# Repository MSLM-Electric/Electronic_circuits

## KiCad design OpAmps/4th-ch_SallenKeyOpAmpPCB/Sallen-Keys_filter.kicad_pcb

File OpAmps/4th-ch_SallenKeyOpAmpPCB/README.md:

!!! PROJECT'S STATUS !!!
Projects is not completed yet.
In progress!
Not tested!

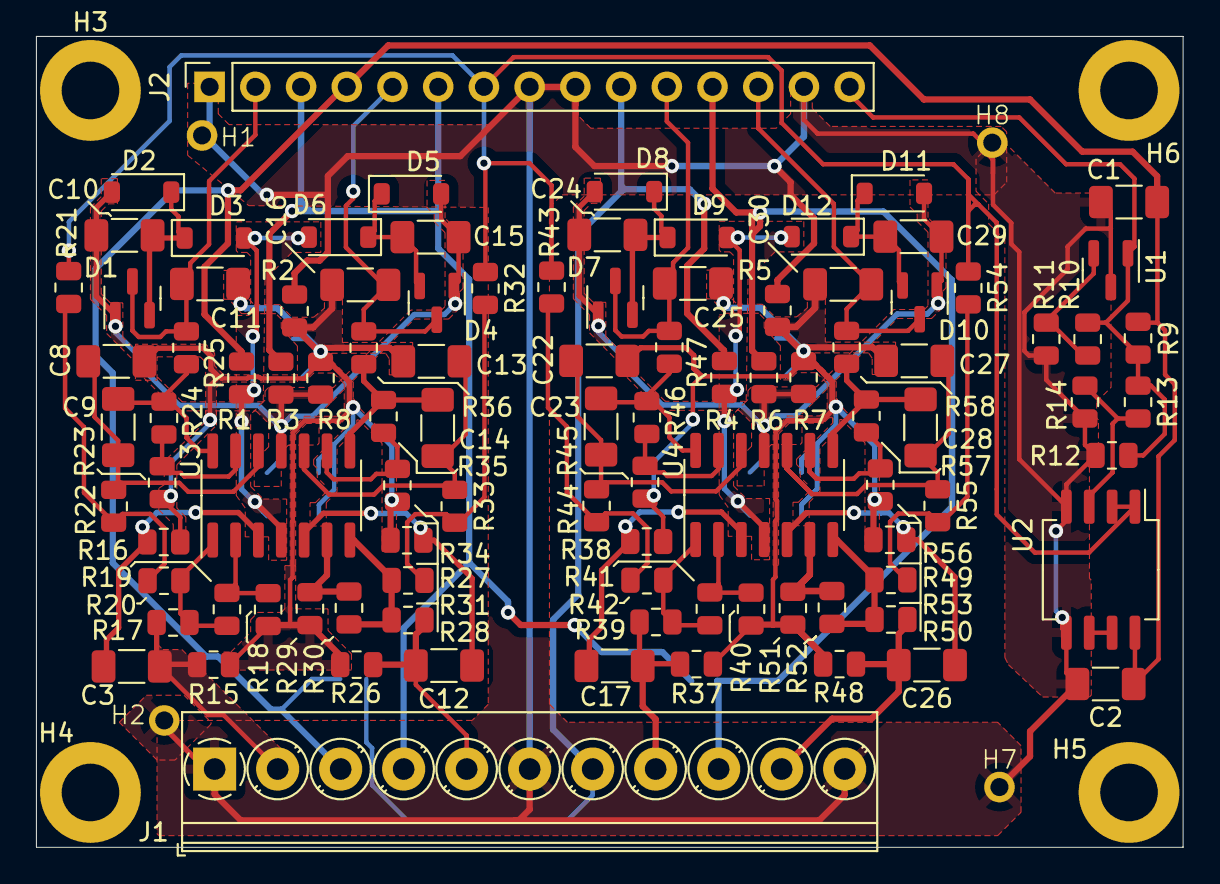
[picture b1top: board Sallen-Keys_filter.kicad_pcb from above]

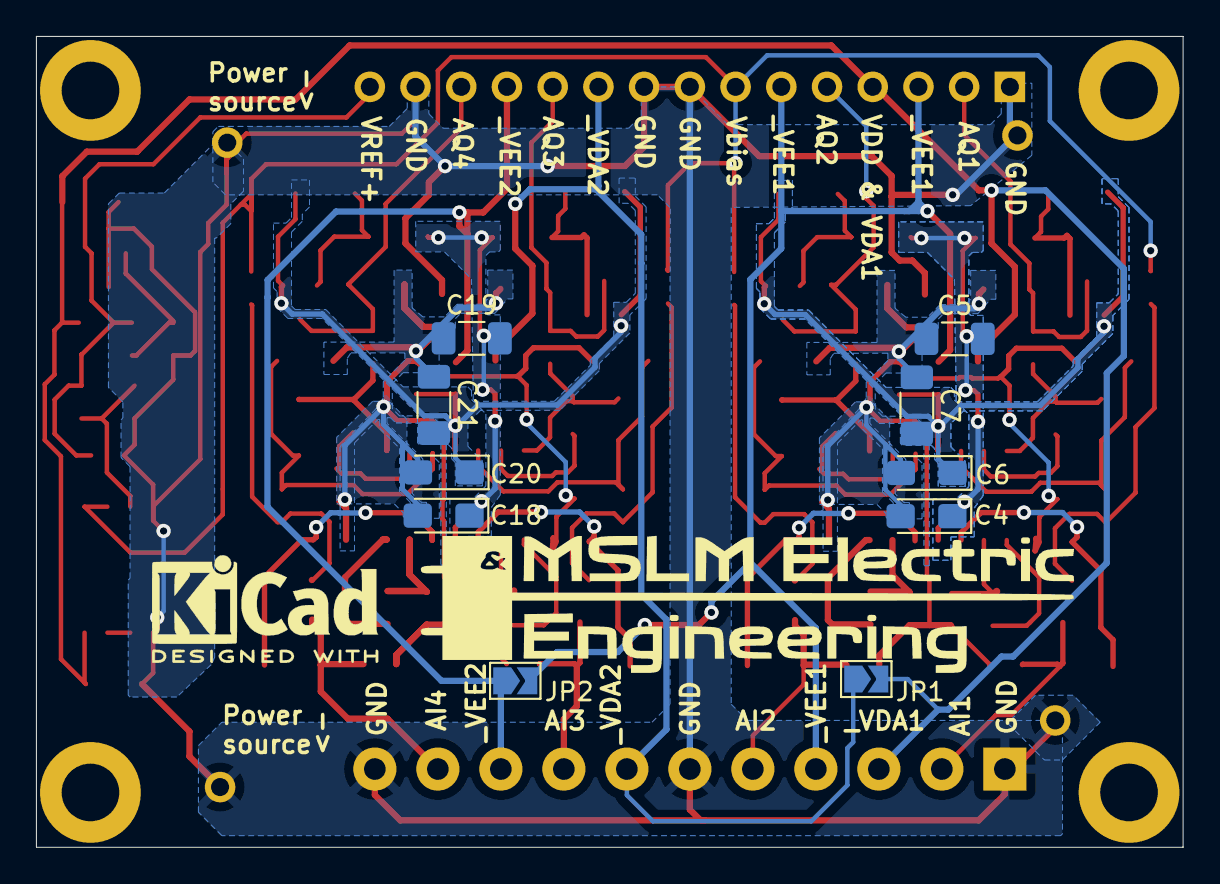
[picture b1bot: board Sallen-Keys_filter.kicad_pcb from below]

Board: 2 copper layers, 63.7 x 45.0 mm, 116 parts (10 on the bottom side), 56 nets.

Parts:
C1, C2, C3, C5, C7, C8, C9, C10, C11, C12, C13, C14, C15, C16, C17, C19, C21, C22, C23, C24, C25, C26, C27, C28, C29, C30: C_Small; C_1206_3216Metric_Pad1.33x1.80mm_HandSolder
C4, C6, C18, C20: CP_Small; CP_EIA-3216-10_Kemet-I_Pad1.58x1.35mm_HandSolder
D1, D4, D7, D10: BAT54S; SOT-23
D2, D5, D8, D11: BZT52C15 /5V1..6/C10; D_SOD-123
D3, D6, D9, D12: 1N4148; D_SOD-123
H1, H2, H7, H8: MountingHole_Pad_small; Hole_pad_1mm
H3, H4, H5, H6: MountingHole_Pad; MountingHole_3.2mm_M3_DIN965_Pad
J1: Screw_Terminal_01x11; TerminalBlock_Phoenix_PT-1,5-11-3.5-H_1x11_P3.50mm_Horizont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
J2: Conn_01x15; PinSocket_1x15_P2.54mm_Vertical
JP1, JP2: Jumper_NC_Small; SolderJumper-2_P1.3mm_Open_TrianglePad1.0x1.5mm
R1, R2, R3, R4, R5, R6: 0R; R_0805_2012Metric
R7, R8: NP; R_0805_2012Metric
R9, R10, R11, R12, R13, R14, R15, R16, R17, R18, R19, R20, R21, R22, R23, R24, R25, R26, R27, R28, R29, R30, R31, R32, R33, R34, R35, R36, R37, R38, R39, R40, R41, R42, R43, R44, R45, R46, R47, R48, R49, R50, R51, R52, R53, R54, R55, R56, R57, R58: R_Small; R_0805_2012Metric
U1: TL431DBZ; SOT-23
U2: LM358; SO-8_5.3x6.2mm_P1.27mm
U3, U4: Opamp_Quad_Generic; SOIC-14_3.9x8.7mm_P1.27mm

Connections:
/AI1: C3.2, J1.2, R15.2, R17.1
/AI2: C12.2, J1.5, R26.2, R28.1
/AI3: C17.2, J1.8, R37.2, R39.1
/AI4: C26.2, J1.10, R48.2, R50.1
/AQ1: C11.2, D1.3 (common), J2.2, R25.1
/AQ2: C16.2, D4.3 (common), J2.5, R36.1
/AQ3: C25.2, D7.3 (common), J2.11, R47.1
/AQ4: C30.2, D10.3 (common), J2.13, R58.1
/OPA1GND: C4.2, C5.1, C6.2, C7.1, C8.1, C11.1, C13.1, C16.1, R2.2, R8.1, R15.1, R16.1, R18.1, R23.1, R26.1, R27.1, R29.1, R34.1
/OPA1VDA: C4.1, C5.2, D3.2 (A), D6.2 (A), R1.2, U3.4 (V+)
/OPA1VEE: C6.1, C7.2, C10.1, C15.1, D1.1 (A), D2.2 (A), D4.1 (A), D5.2 (A), R3.2, R8.2, U3.11 (V-)
/OPA2GND: C18.2, C19.1, C20.2, C21.1, C22.1, C25.1, C27.1, C30.1, R5.2, R7.1, R37.1, R38.1, R40.1, R45.1, R48.1, R49.1, R51.1, R56.1
/OPA2VDA: C18.1, C19.2, D9.2 (A), D12.2 (A), R4.2, U4.4 (V+)
/OPA2VEE: C20.1, C21.2, C24.1, C29.1, D7.1 (A), D8.2 (A), D10.1 (A), D11.2 (A), R6.2, R7.2, U4.11 (V-)
/VBIAS1/EN: C1.1, C2.1, J1.3, J2.4, JP1.2, R1.1, R9.2, U2.8 (V+)
/VREF+: J2.15, R9.1, R10.1, R12.1, R13.1, U1.1 (K)
/bias: J2.7, R21.1, R32.1, R43.1, R54.1, U2.1, U2.2 (-)
GNDD: C1.2, C2.2, H1.1, H2.1, H7.1, H8.1, J1.1, J1.6, J1.11, J2.1, J2.8, J2.9, J2.14, R2.1, R5.1, R11.2, R12.2, R14.2, U1.3 (A), U2.4 (V-), U2.5 (+)
unnamed: C9.1, R24.1, R25.2, U3.14
unnamed: C14.1, R35.1, R36.2, U3.8
unnamed: C23.1, R46.1, R47.2, U4.14
unnamed: C28.1, R57.1, R58.2, U4.8
unnamed: C10.2, D1.2 (K), D2.1 (K), D3.1 (K)
unnamed: C15.2, D4.2 (K), D5.1 (K), D6.1 (K)
unnamed: C24.2, D7.2 (K), D8.1 (K), D9.1 (K)
unnamed: C29.2, D10.2 (K), D11.1 (K), D12.1 (K)
unnamed: J1.4, J2.3, J2.6, JP2.2, R3.1
unnamed: J1.7, J2.10, JP1.1, R4.1
unnamed: J1.9, J2.12, JP2.1, R6.1
unnamed: R17.2, R19.1, R20.2, U3.1
unnamed: R20.1, R21.2, R22.2
unnamed: R28.2, R30.1, R31.2, U3.7
unnamed: R31.1, R32.2, R33.2
unnamed: R39.2, R41.1, R42.2, U4.1
unnamed: R42.1, R43.2, R44.2
unnamed: R50.2, R52.1, R53.2, U4.7
unnamed: R53.1, R54.2, R55.2
unnamed: R10.2, R11.1, U1.2 (REF)
unnamed: R13.2, R14.1, U2.3 (+)
unnamed: U2.6 (-), U2.7
unnamed: C3.1, R16.2, U3.3 (+)
unnamed: R18.2, R19.2, U3.2 (-)
unnamed: C12.1, R27.2, U3.5 (+)
unnamed: R29.2, R30.2, U3.6 (-)
unnamed: C13.2, C14.2, R33.1, U3.10 (+)
unnamed: R34.2, R35.2, U3.9 (-)
unnamed: C8.2, C9.2, R22.1, U3.12 (+)
unnamed: R23.2, R24.2, U3.13 (-)
unnamed: C17.1, R38.2, U4.3 (+)
unnamed: R40.2, R41.2, U4.2 (-)
unnamed: C26.1, R49.2, U4.5 (+)
unnamed: R51.2, R52.2, U4.6 (-)
unnamed: C27.2, C28.2, R55.1, U4.10 (+)
unnamed: R56.2, R57.2, U4.9 (-)
unnamed: C22.2, C23.2, R44.1, U4.12 (+)
unnamed: R45.2, R46.2, U4.13 (-)

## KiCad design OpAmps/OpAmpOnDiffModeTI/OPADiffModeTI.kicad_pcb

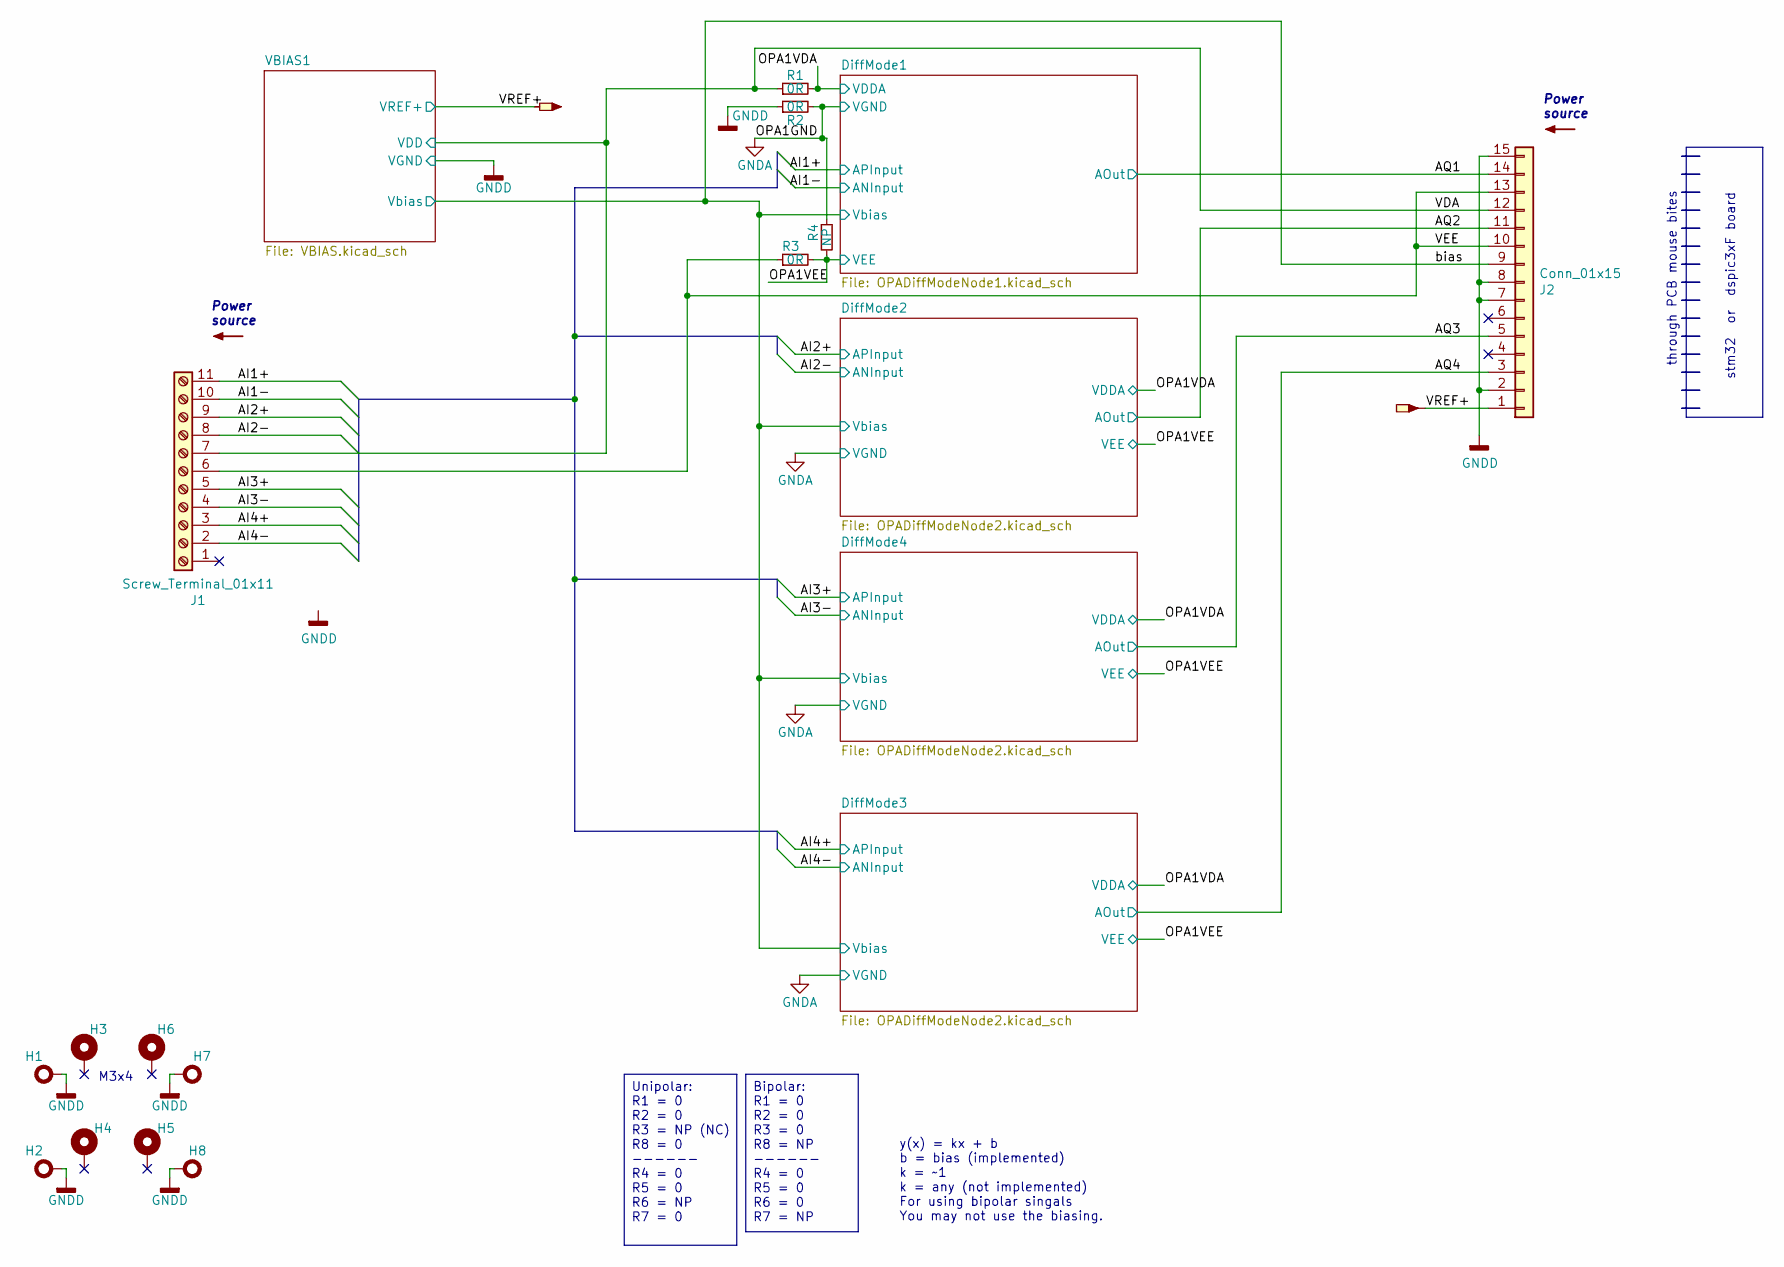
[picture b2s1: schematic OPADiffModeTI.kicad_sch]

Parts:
H1, H2, H7, H8: MountingHole_Pad_small; Hole_pad_1mm
H3, H4, H5, H6: MountingHole_Pad; MountingHole_3.2mm_M3_DIN965_Pad
J1: Screw_Terminal_01x11; TerminalBlock_Phoenix_PT-1,5-11-3.5-H_1x11_P3.50mm_Horizont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
J2: Conn_01x15; PinSocket_1x15_P2.54mm_Vertical
R1, R2, R3: 0R; R_0805_2012Metric
R4: NP; R_0805_2012Metric

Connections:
/AI1+: J1.11; also elsewhere on the board
/AI1-: J1.10; also elsewhere on the board
/AI2+: J1.9; also elsewhere on the board
/AI2-: J1.8; also elsewhere on the board
/AI3+: J1.5; also elsewhere on the board
/AI3-: J1.4; also elsewhere on the board
/AI4+: J1.3; also elsewhere on the board
/AI4-: J1.2; also elsewhere on the board
/AQ1: J2.14; also elsewhere on the board
/AQ2: J2.11; also elsewhere on the board
/AQ3: J2.5; also elsewhere on the board
/AQ4: J2.3; also elsewhere on the board
/OPA1VDA: R1.2; also elsewhere on the board
/OPA1VEE: R3.2, R4.2; also elsewhere on the board
/VDA: J1.7, J2.12, R1.1; also elsewhere on the board
/VEE: J1.6, J2.10, J2.13, R3.1
/VREF+: J2.1; also elsewhere on the board
/bias: J2.9; also elsewhere on the board
GNDA: R2.2, R4.1; also elsewhere on the board
GNDD: H1.1, H2.1, H7.1, H8.1, J2.2, J2.7, J2.8, J2.15, R2.1; also elsewhere on the board

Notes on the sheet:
Power source
у(x) = kx + b b = bias (implemented) k = ~1 k = any (not implemented) For using bipolar singals You may not use the biasing.
through PCB mouse bites
stm32 or dspic3xF board
M3x4
Bipolar: R1 = 0 R2 = 0 R3 = 0 R8 = NP ------ R4 = 0 R5 = 0 R6 = 0 R7 = NP
Unipolar: R1 = 0 R2 = 0 R3 = NP (NC) R8 = 0 ------ R4 = 0 R5 = 0 R6 = NP R7 = 0

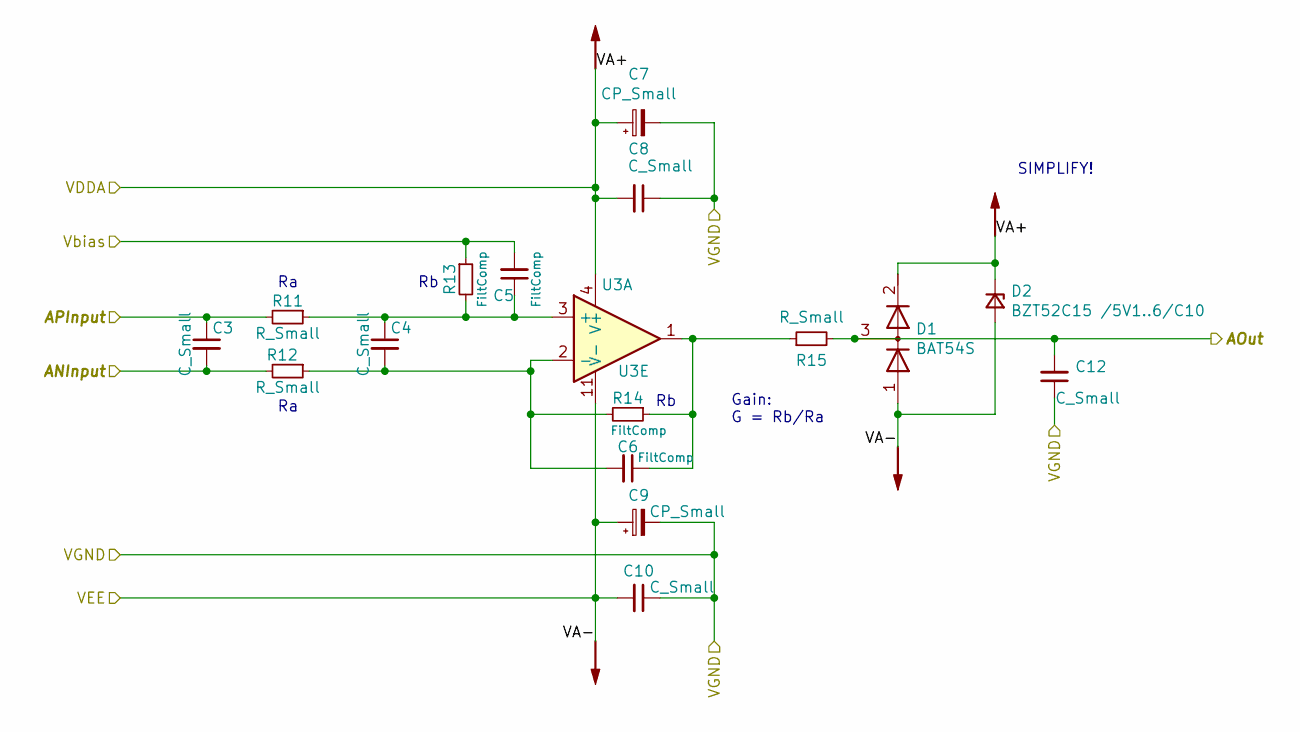
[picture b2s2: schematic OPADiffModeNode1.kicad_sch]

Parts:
C3, C4, C8, C10, C12: C_Small; C_1206_3216Metric_Pad1.33x1.80mm_HandSolder
C5, C6: FiltComp; C_1206_3216Metric_Pad1.33x1.80mm_HandSolder
C7, C9: CP_Small; CP_EIA-3216-10_Kemet-I_Pad1.58x1.35mm_HandSolder
D1: BAT54S; SOT-23
D2: BZT52C15 /5V1..6/C10; D_SOD-123
R11, R12, R15: R_Small; R_0805_2012Metric
R13, R14: FiltComp; R_0805_2012Metric
U3: Opamp_Quad_Generic; SOIC-14_3.9x8.7mm_P1.27mm

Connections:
/AI1+: C3.1, R11.2; also elsewhere on the board
/AI1-: C3.2, R12.2; also elsewhere on the board
/AQ1: C12.2, D1.3 (common), R15.2; also elsewhere on the board
/OPA1VDA: C7.1, C8.2, D1.2 (K), D2.1 (K), U3.4 (V+); also elsewhere on the board
/OPA1VEE: C9.1, C10.2, D1.1 (A), D2.2 (A), U3.11 (V-); also elsewhere on the board
/bias: C5.2, R13.1; also elsewhere on the board
GNDA: C7.2, C8.1, C9.2, C10.1, C12.1; also elsewhere on the board
unnamed: C6.1, R14.1, R15.1, U3.1
unnamed 22: U3.8; also elsewhere on the board
unnamed 23: U3.14; also elsewhere on the board
unnamed: C4.1, C5.1, R11.1, R13.2, U3.3 (+)
unnamed: C4.2, C6.2, R12.1, R14.2, U3.2 (-)
unnamed 31: U3.10 (+); also elsewhere on the board
unnamed 32: U3.9 (-); also elsewhere on the board
unnamed 33: U3.12 (+); also elsewhere on the board
unnamed 34: U3.13 (-); also elsewhere on the board

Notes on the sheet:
SIMPLIFY!
Gain: G = Rb/Ra

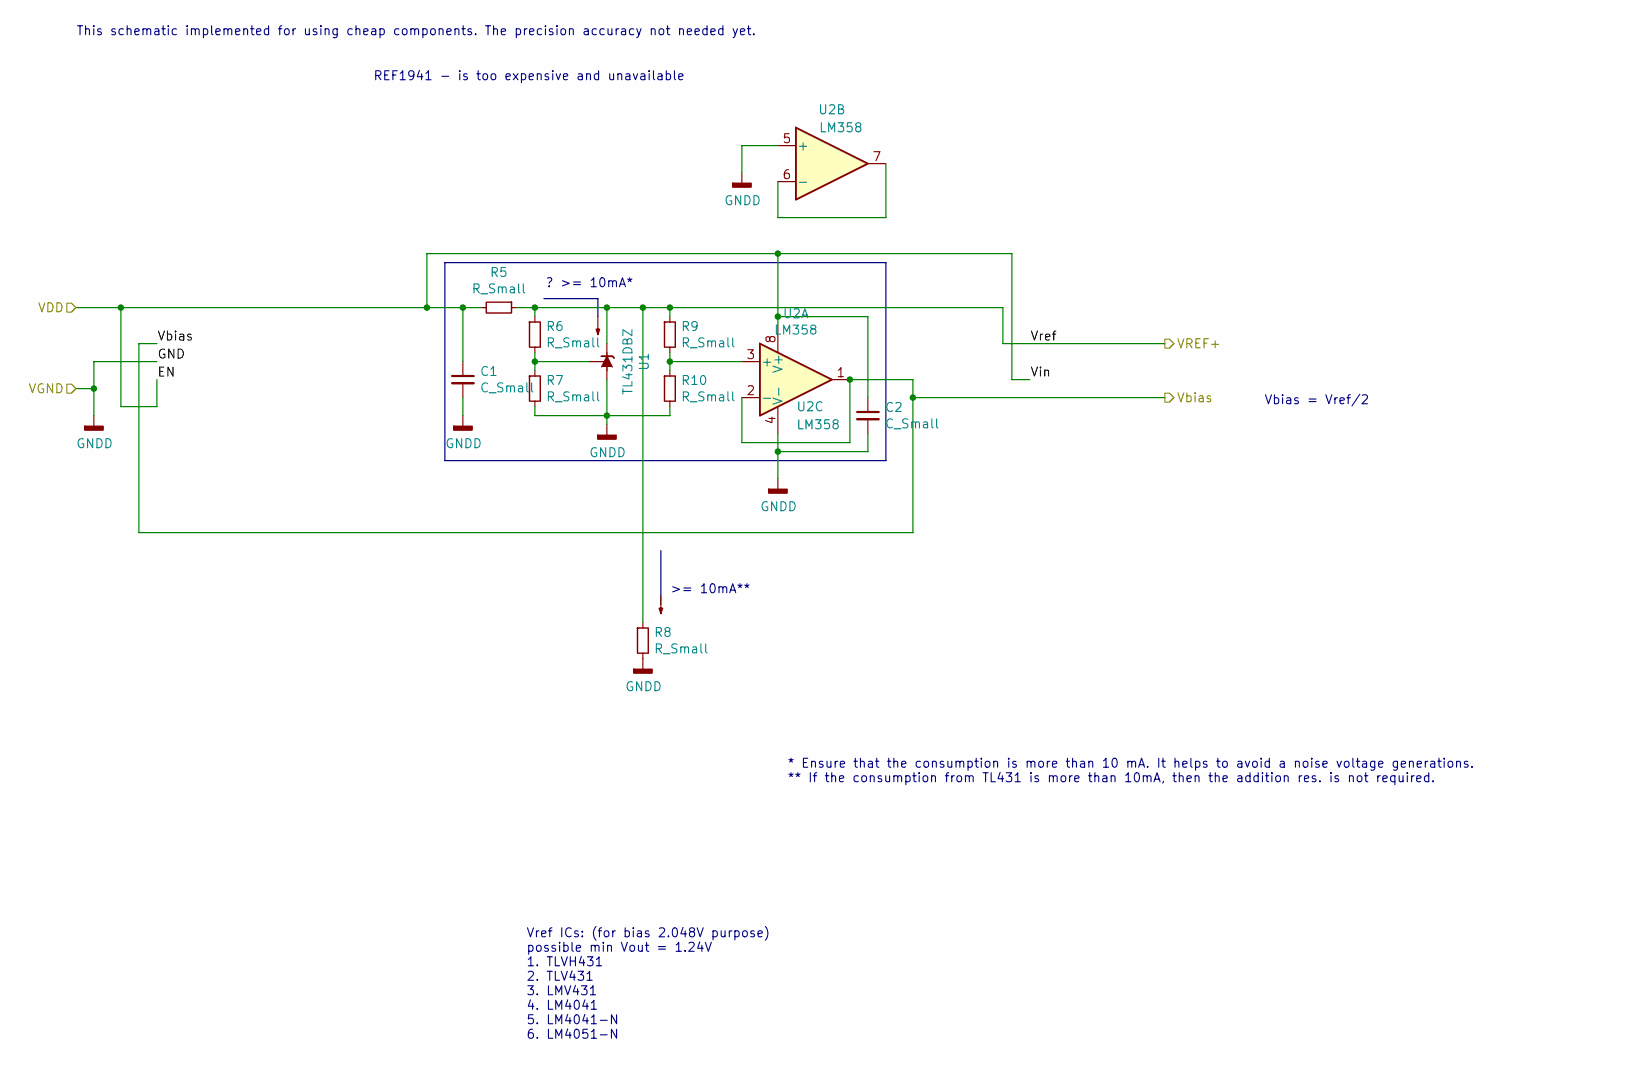
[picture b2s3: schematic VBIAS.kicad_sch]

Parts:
C1, C2: C_Small; C_1206_3216Metric_Pad1.33x1.80mm_HandSolder
R5, R6, R7, R8, R9, R10: R_Small; R_0805_2012Metric
U1: TL431DBZ; SOT-23
U2: LM358; SO-8_5.3x6.2mm_P1.27mm

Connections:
/VDA: C1.1, C2.1, R5.2, U2.8 (V+); also elsewhere on the board
/VREF+: R5.1, R6.1, R8.1, R9.1, U1.1 (K); also elsewhere on the board
/bias: U2.1, U2.2 (-); also elsewhere on the board
GNDD: C1.2, C2.2, R7.2, R8.2, R10.2, U1.3 (A), U2.4 (V-), U2.5 (+); also elsewhere on the board
unnamed: R6.2, R7.1, U1.2 (REF)
unnamed: R9.2, R10.1, U2.3 (+)
unnamed: U2.6 (-), U2.7

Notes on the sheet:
REF1941 - is too expensive and unavailable
Vref ICs: (for bias 2.048V purpose) possible min Vout = 1.24V 1. TLVH431 2. TLV431 3. LMV431 4. LM4041 5. LM4041-N 6. LM4051-N
Vbias = Vref/2
>= 10mA**
* Ensure that the consumption is more than 10 mA. It helps to avoid a noise voltage generations. ** If the consumption from TL431 is more than 10mA, then the addition res. is not required.
? >= 10mA*
This schematic implemented for using cheap components. The precision accuracy not needed yet.

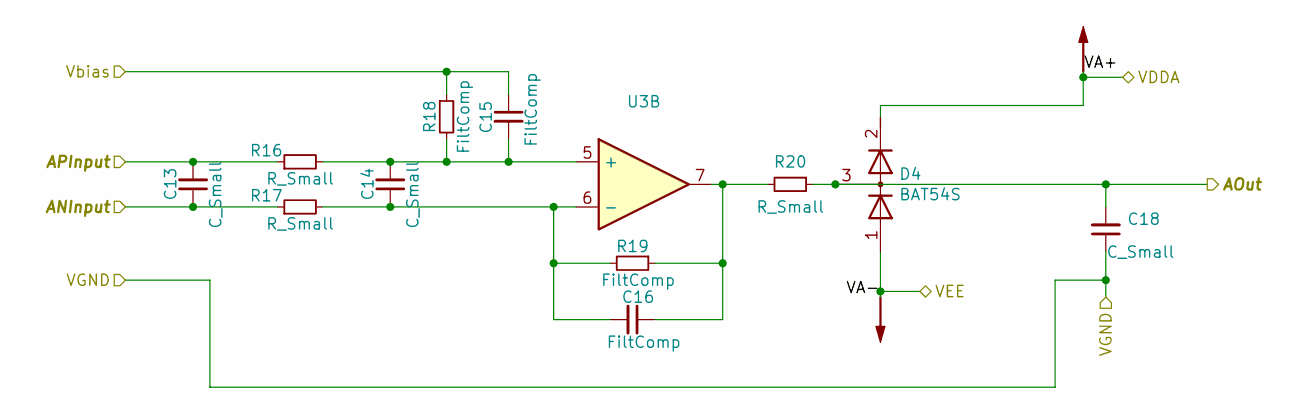
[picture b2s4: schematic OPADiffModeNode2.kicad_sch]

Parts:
C13, C14, C18: C_Small; C_1206_3216Metric_Pad1.33x1.80mm_HandSolder
C15, C16: FiltComp; C_1206_3216Metric_Pad1.33x1.80mm_HandSolder
D4: BAT54S; SOT-23
R16, R17, R20: R_Small; R_0805_2012Metric
R18, R19: FiltComp; R_0805_2012Metric
U3: Opamp_Quad_Generic; SOIC-14_3.9x8.7mm_P1.27mm

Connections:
/AI2+: C13.2, R16.1; also elsewhere on the board
/AI2-: C13.1, R17.1; also elsewhere on the board
/AQ2: C18.2, D4.3 (common), R20.1; also elsewhere on the board
/OPA1VDA: D4.2 (K); also elsewhere on the board
/OPA1VEE: D4.1 (A); also elsewhere on the board
/bias: C15.1, R18.1; also elsewhere on the board
GNDA: C18.1; also elsewhere on the board
unnamed: C16.1, R19.1, R20.2, U3.7
unnamed 22: U3.8; also elsewhere on the board
unnamed 23: U3.14; also elsewhere on the board
unnamed: C14.2, C15.2, R16.2, R18.2, U3.5 (+)
unnamed: C14.1, C16.2, R17.2, R19.2, U3.6 (-)
unnamed 31: U3.10 (+); also elsewhere on the board
unnamed 32: U3.9 (-); also elsewhere on the board
unnamed 33: U3.12 (+); also elsewhere on the board
unnamed 34: U3.13 (-); also elsewhere on the board

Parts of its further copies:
C19, C20, C24, C25, C26, C30: C_Small; C_1206_3216Metric_Pad1.33x1.80mm_HandSolder
C21, C22, C27, C28: FiltComp; C_1206_3216Metric_Pad1.33x1.80mm_HandSolder
D5, D6: BAT54S; SOT-23
R21, R22, R25, R26, R27, R30: R_Small; R_0805_2012Metric
R23, R24, R28, R29: FiltComp; R_0805_2012Metric

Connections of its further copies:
/AI3+: C25.2, R26.1; also elsewhere on the board
/AI3-: C25.1, R27.1; also elsewhere on the board
/AI4+: C19.2, R21.1; also elsewhere on the board
/AI4-: C19.1, R22.1; also elsewhere on the board
/AQ3: C30.2, D6.3 (common), R30.1; also elsewhere on the board
/AQ4: C24.2, D5.3 (common), R25.1; also elsewhere on the board
/OPA1VDA: D5.2 (K), D6.2 (K); also elsewhere on the board
/OPA1VEE: D5.1 (A), D6.1 (A); also elsewhere on the board
/bias: C21.1, C27.1, R23.1, R28.1; also elsewhere on the board
GNDA: C24.1, C30.1; also elsewhere on the board
unnamed 22: C22.1, R24.1, R25.2; also elsewhere on the board
unnamed 23: C28.1, R29.1, R30.2; also elsewhere on the board
unnamed 31: C20.2, C21.2, R21.2, R23.2; also elsewhere on the board
unnamed 32: C20.1, C22.2, R22.2, R24.2; also elsewhere on the board
unnamed 33: C26.2, C27.2, R26.2, R28.2; also elsewhere on the board
unnamed 34: C26.1, C28.2, R27.2, R29.2; also elsewhere on the board

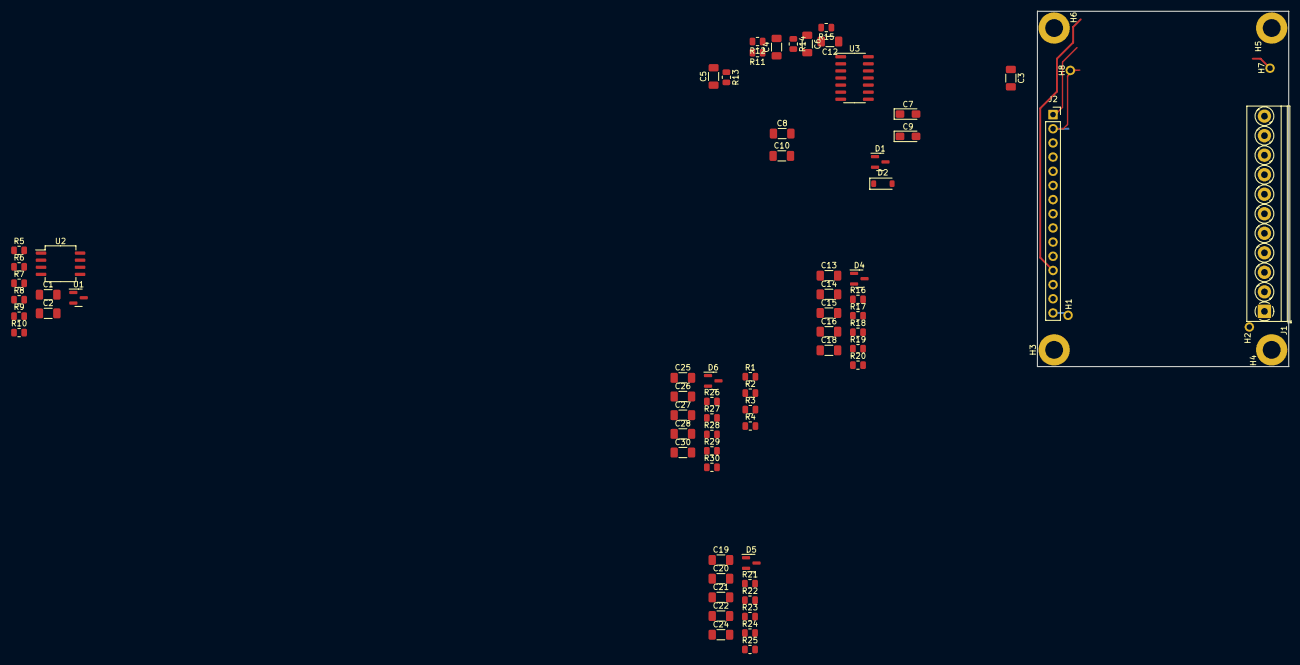
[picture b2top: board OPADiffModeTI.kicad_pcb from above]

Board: 2 copper layers, 45.1 x 63.7 mm, 74 parts (0 on the bottom side), 35 nets.

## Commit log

2023-12-15 Bismillah!
2023-12-15 seconda!
2023-12-15 KiCad workings
2023-12-26 Full schematic
2023-12-26 Anaconda! Power source direction described
2023-12-26 fourtha!
2023-12-26 fiftha!
2023-12-28 Vref Vbias scheme added
2024-03-28 Biasing single SallKe. Opamp
2024-03-28 remove extra
2024-06-07 separate gnds added
2024-06-14 scheme update
2024-11-08 kicad hotkeys
2024-12-24 warned about mistake in scheme!
2024-12-27 ssop to soic mini pcb & diff mode 4 opa
2024-12-28 opa diff mode jobs
2025-10-31 few works before new branch
2025-10-31 smdel
